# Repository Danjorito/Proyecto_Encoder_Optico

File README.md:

# Github del proyecto del grupo 5

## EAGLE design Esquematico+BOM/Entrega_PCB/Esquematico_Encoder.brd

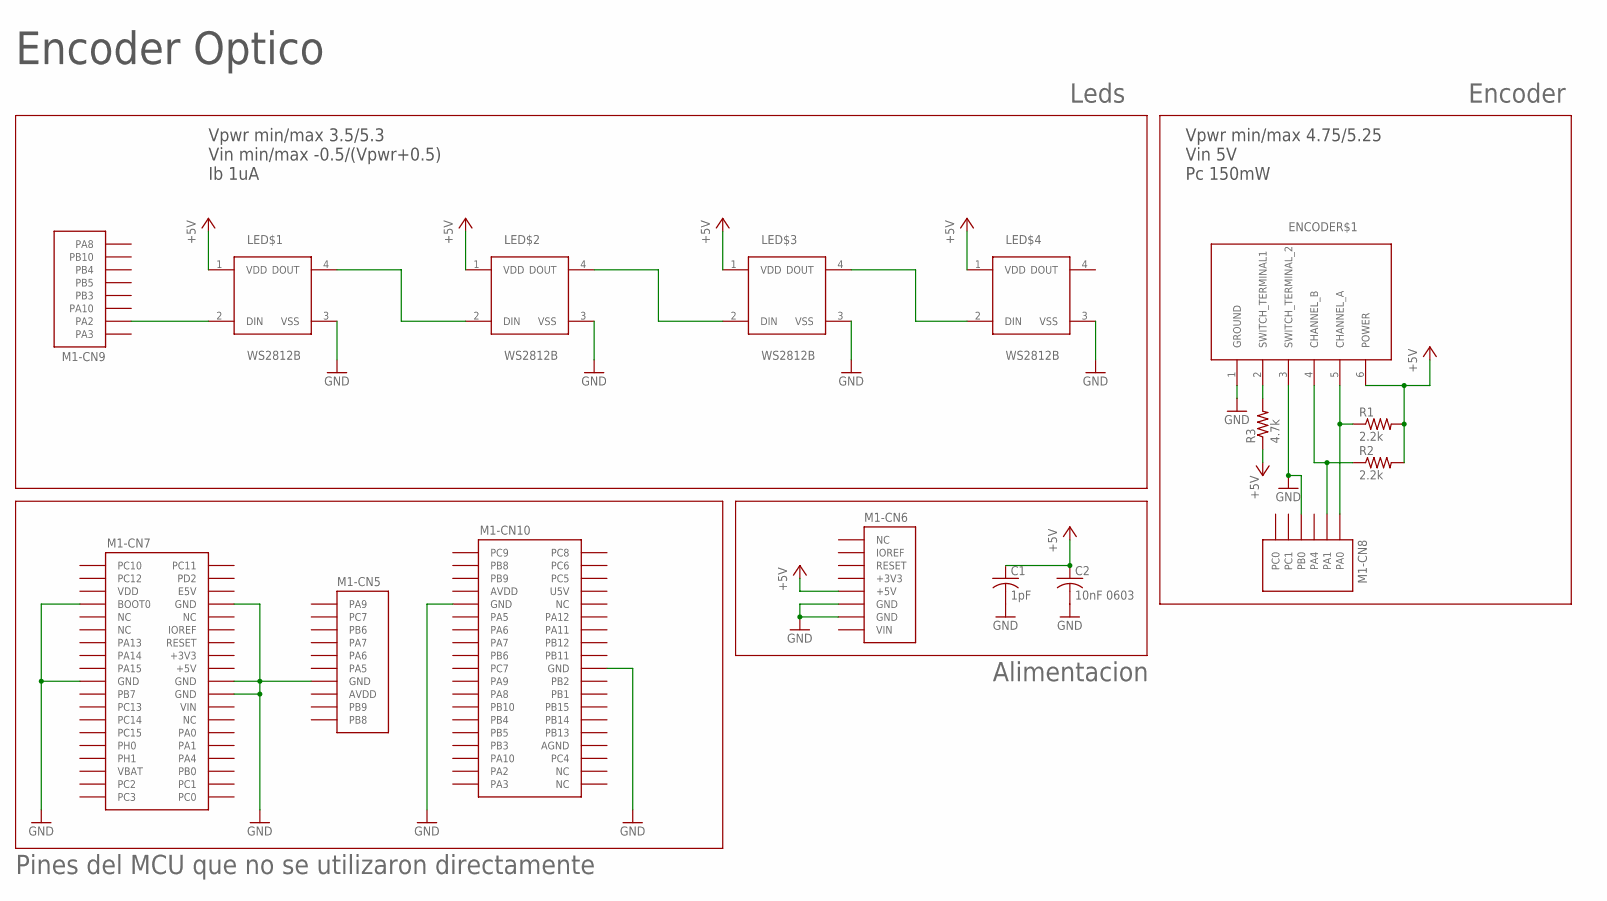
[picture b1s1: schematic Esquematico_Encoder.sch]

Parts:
C1: 1pF; C0805; PARTNO GCM21BR71E105KA56L
C2: 10nF 0603; C0603; PARTNO GCM188R72A103KA37D
ENCODER$1: 291V1022F832AB; TRAY; PARTNO 291V1022F832AB
LED$1, LED$2, LED$3, LED$4: WS2812B; PARTNO WS2812B
M1: NUCLEO-L452RE; NUCLEO-64
R1, R2: 2.2k; R0805; PARTNO CR0805-JW-222ELF
R3: 4.7k; R0805; PARTNO RC0805FR-074K7L

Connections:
+3V3: M1.CN6-4 (+3V3), M1.CN7-16 (+3V3)
+5V: C1.1, C2.1, ENCODER$1.6 (POWER), LED$1.1 (VDD), LED$2.1 (VDD), LED$3.1 (VDD), LED$4.1 (VDD), M1.CN6-5 (+5V), M1.CN7-18 (+5V), R1.2, R2.2, R3.1
AGND: M1.CN10-32 (AGND)
AVDD: M1.CN5-8 (AVDD), M1.CN10-7 (AVDD)
GND: C1.2, C2.2, ENCODER$1.1 (GROUND), ENCODER$1.3 (SWITCH_TERMINAL_2), LED$1.3 (VSS), LED$2.3 (VSS), LED$3.3 (VSS), LED$4.3 (VSS), M1.CN5-7 (GND), M1.CN6-6 (GND), M1.CN6-7 (GND), M1.CN7-7 (BOOT0), M1.CN7-8 (GND), M1.CN7-19 (GND), M1.CN7-20 (GND), M1.CN7-22 (GND), M1.CN8-4 (PB0), M1.CN10-9 (GND), M1.CN10-20 (GND)
IOREF: M1.CN6-2 (IOREF)
unnamed: LED$1.4 (DOUT), LED$2.2 (DIN)
unnamed: LED$2.4 (DOUT), LED$3.2 (DIN)
unnamed: LED$3.4 (DOUT), LED$4.2 (DIN)
unnamed: ENCODER$1.5 (CHANNEL_A), M1.CN8-1 (PA0), R1.1
unnamed: ENCODER$1.4 (CHANNEL_B), M1.CN8-2 (PA1), R2.1
unnamed: ENCODER$1.2 (SWITCH_TERMINAL1), R3.2
unnamed: LED$1.2 (DIN), M1.CN9-2 (PA2)
U5V: M1.CN10-8 (U5V)
VBAT: M1.CN7-33 (VBAT)
VDD: M1.CN7-5 (VDD)
VIN: M1.CN6-8 (VIN), M1.CN7-24 (VIN)

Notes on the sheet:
Encoder Optico
Vpwr min/max 3.5/5.3 Vin min/max -0.5/(Vpwr+0.5) Ib 1uA
Vpwr min/max 4.75/5.25 Vin 5V Pc 150mW
Leds
Encoder
Alimentacion
Pines del MCU que no se utilizaron directamente

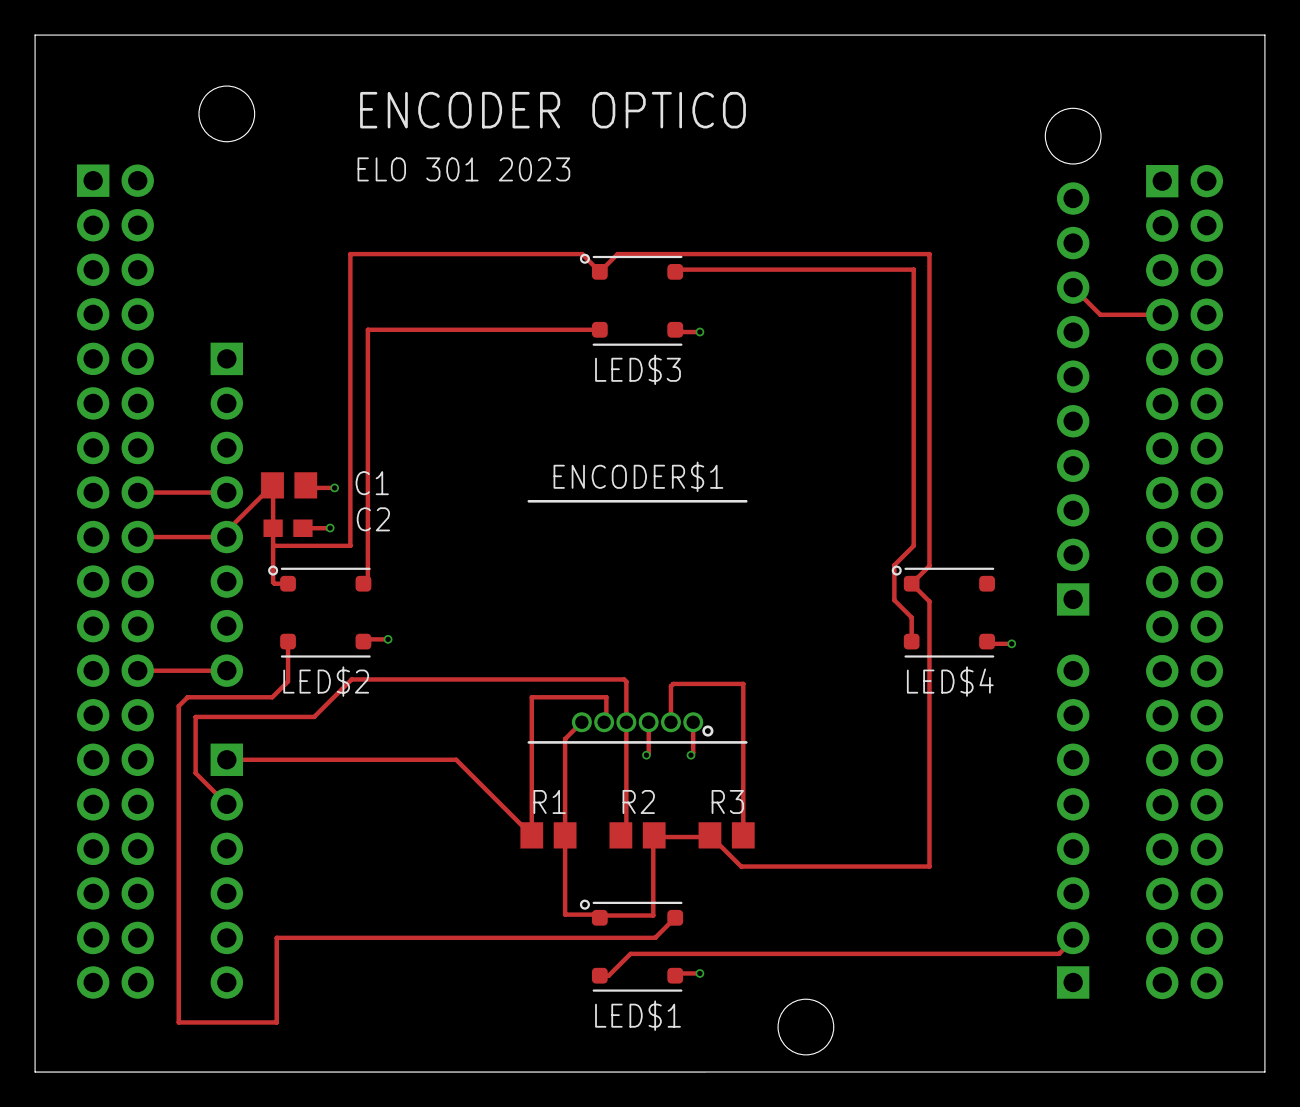
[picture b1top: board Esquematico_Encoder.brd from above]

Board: 2 copper layers, 70.1 x 59.1 mm, 11 parts (0 on the bottom side), 12 nets.

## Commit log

2023-10-19 Added schematic and BOM
2023-10-29 Se agregaron archivos de la entrega de PCB
2023-11-30 Added the firmware
